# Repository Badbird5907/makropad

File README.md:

# Makropad

Makropad is my attempt at a custom macropad, inspired by the [Stream Deck Plus](https://www.elgato.com/ca/en/p/stream-deck-plus-black).
It uses Kaith Choc v2 switches, 2 encoders, powered by a RP2040.

A user-friendly BOM can be found [here](https://github.com/Badbird5907/makropad/blob/master/PCB/BOM.md)

## Features
- 2 rotary encoders
- 10 backlit keys
- 128x32 OLED display

## Screenshots

3D Renders of the Cherry MX switch version (made with Shapr3D):

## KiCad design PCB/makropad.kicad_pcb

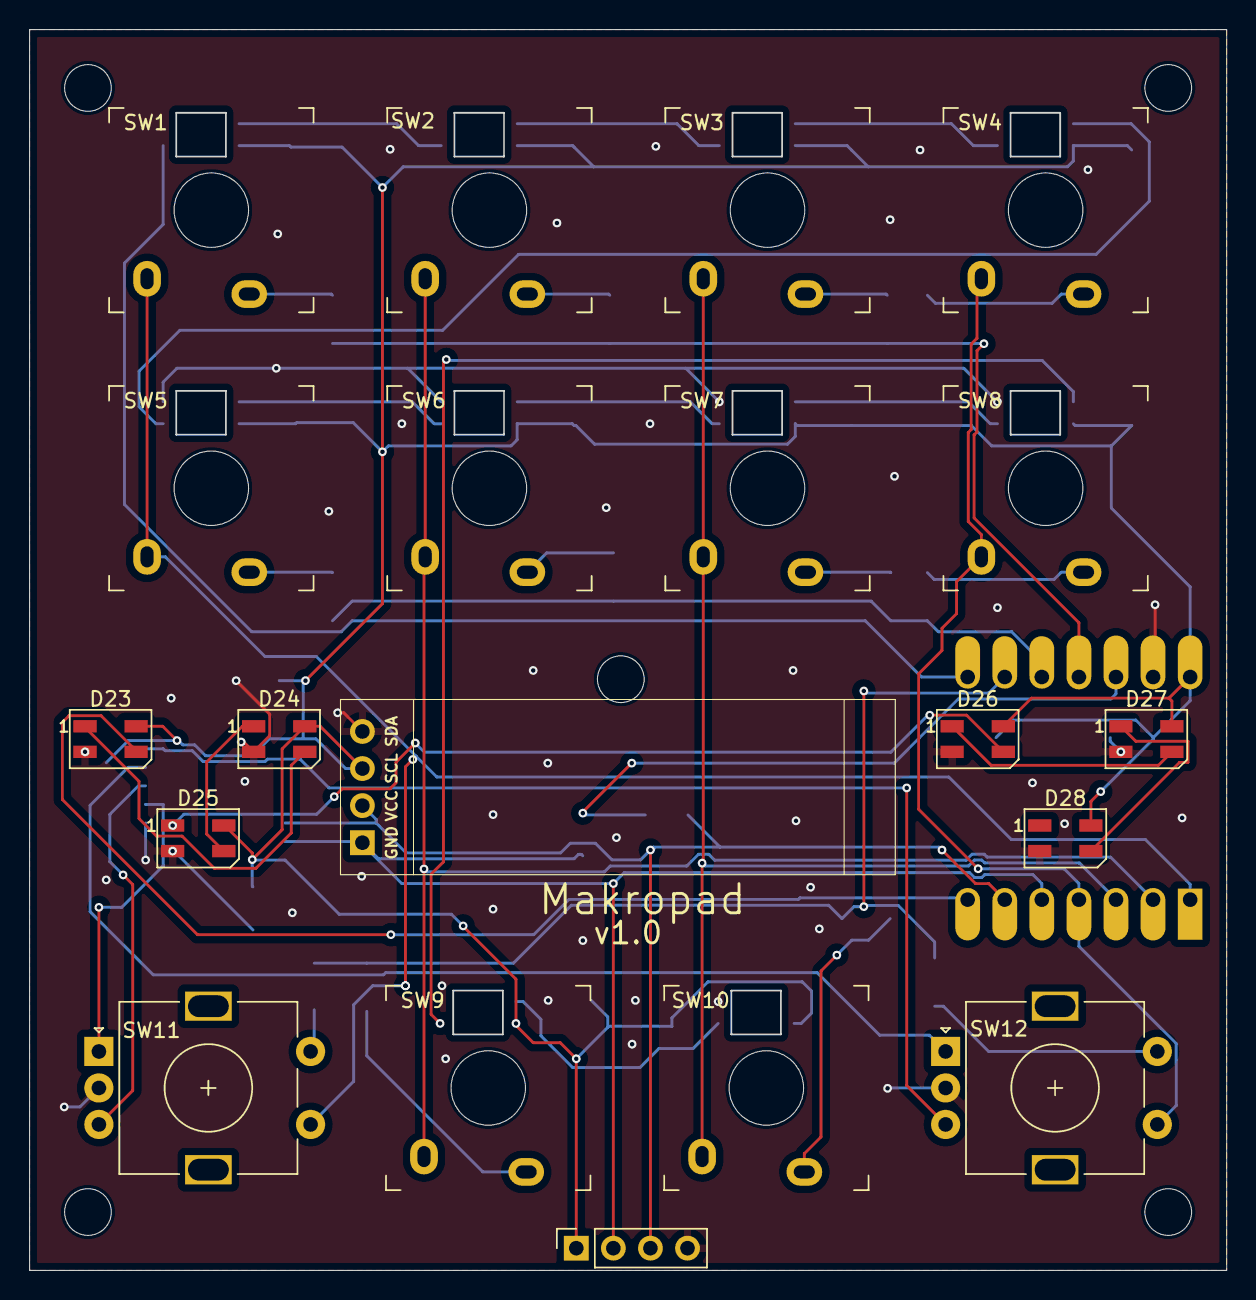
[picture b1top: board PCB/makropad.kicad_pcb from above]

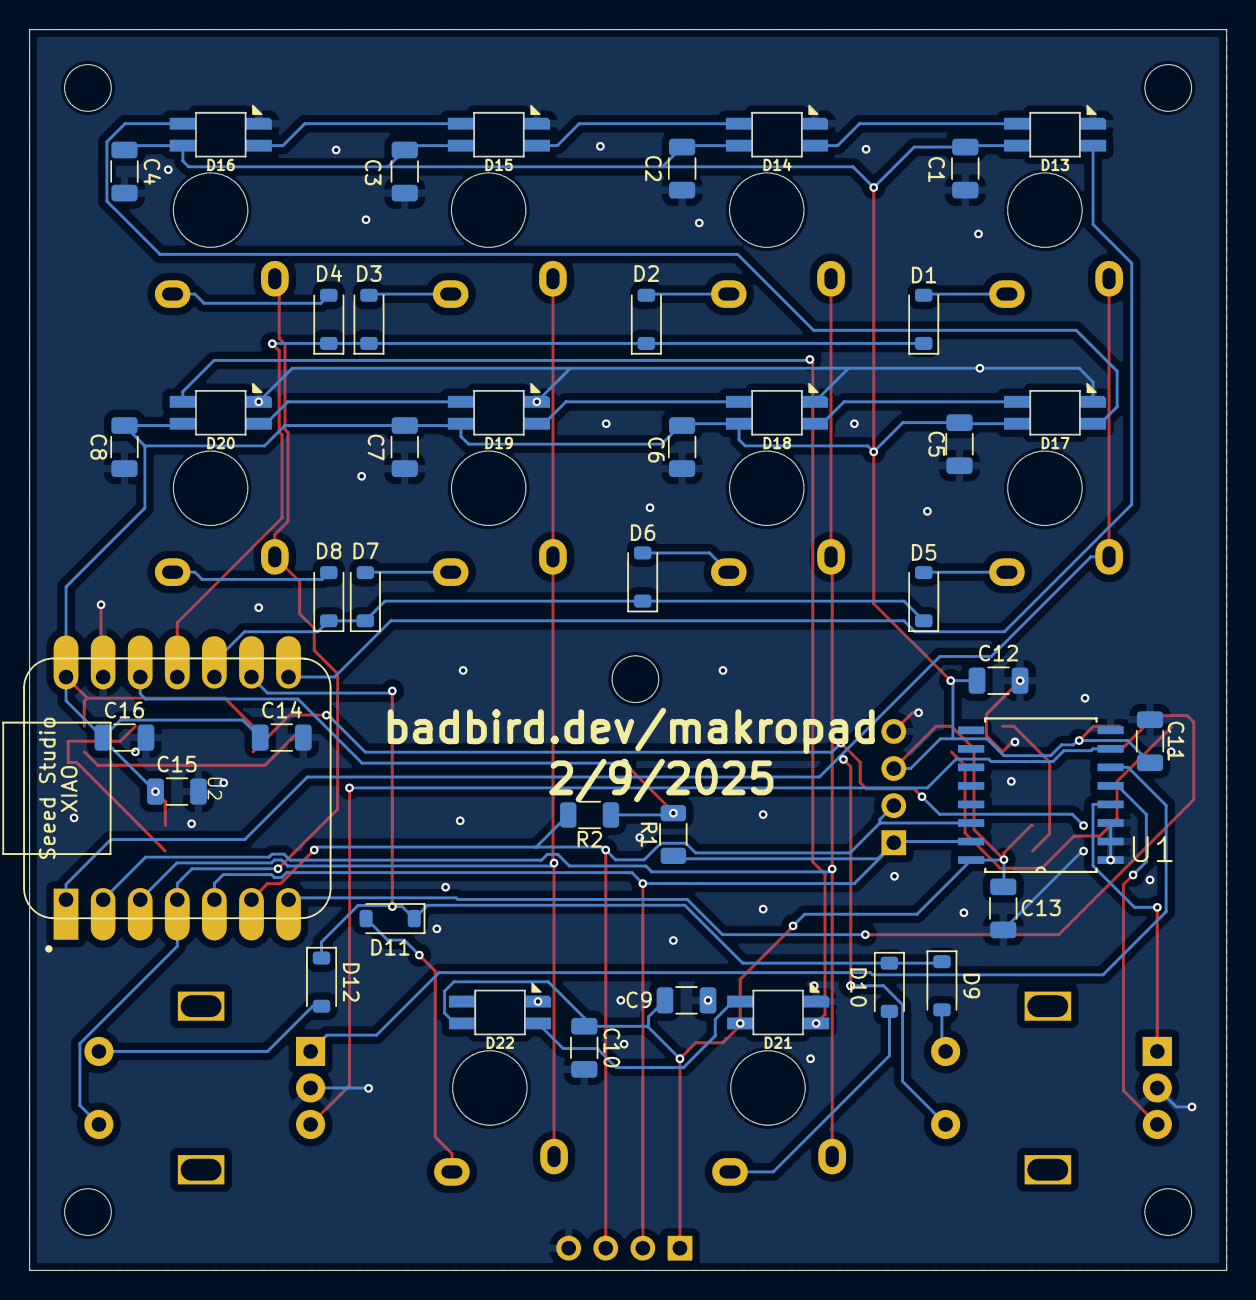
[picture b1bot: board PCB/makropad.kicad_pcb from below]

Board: 2 copper layers, 82.0 x 85.0 mm, 67 parts (43 on the bottom side), 44 nets.

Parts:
C1, C2, C3, C4, C5, C6, C7, C8, C9, C10, C11, C12, C13, C14, C15, C16: 0.1uF; C_1206_3216Metric
D1, D2, D3, D4, D5, D6, D7, D8, D9, D10, D11, D12: D; D_SOD-123
D13, D14, D15, D16, D17, D18, D19, D20, D21, D22: SK6812; SK6812MINI-E
D23, D24, D25, D26, D27, D28: SK6812; LED_SK6812MINI_PLCC4_3.5x3.5mm_P1.75mm
J1: OLED_DISPLAY; SSD1306-0.91-OLED-4pin-128x32
J2: Conn_01x04; 4pin
MH1, MH2, MH3, MH4, MH5: MountingHole_3.2mm_M3
R1, R2: 10k; R_1206_3216Metric
SW1, SW2, SW3, SW4, SW5, SW6, SW7, SW8, SW9, SW10: SW_Push_45deg; Gateron Low Profile Switch 2.0
SW11, SW12: RotaryEncoder_Switch; encoder
U1: PCF8574A; SOIC127P1032X265-16N
U2: MOUDLE-SEEEDUINO-XIAO; XIAO-Generic-Hybrid-14P-2.54-21X17.8MM

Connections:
+3.3V: R1.2, R2.2, U2.12 (3V3)
COL0: SW1.1, SW5.1, SW11.S1, U2.1 (PA02_A0_D0)
COL1: SW2.1, SW6.1, SW9.1, U2.2 (PA4_A1_D1)
COL2: SW3.1, SW7.1, SW10.1, U2.3 (PA10_A2_D2)
COL3: SW4.1, SW8.1, SW12.S1, U2.4 (PA11_A3_D3)
ENC_1_A: SW11.A, U1.4 (P0)
ENC_1_B: SW11.B, U1.5 (P1)
ENC_1_SWA: D9.2 (A), SW11.S2
ENC_2_A: SW12.A, U1.6 (P2)
ENC_2_B: SW12.B, U1.7 (P3)
ENC_2_SWA: D12.2 (A), SW12.S2
GND: C1.2, C2.2, C3.2, C4.2, C5.2, C6.2, C7.2, C8.2, C9.2, C10.2, C11.2, C12.2, C13.2, C14.2, C15.2, C16.2, D13.2 (VSS), D14.2 (VSS), D15.2 (VSS), D16.2 (VSS), D17.2 (VSS), D18.2 (VSS), D19.2 (VSS), D20.2 (VSS), D21.2 (VSS), D22.2 (VSS), D23.2 (VSS), D24.2 (VSS), D25.2 (VSS), D26.2 (VSS), D27.2 (VSS), D28.2 (VSS), J1.4, J2.4, SW11.C, SW12.C, U1.1 (A0), U1.2 (A1), U1.3 (A2), U1.8 (VSS), U2.13 (GND)
I2C_SCL: J1.2, J2.3, R2.1, U1.14 (SCL), U2.6 (PA9_A5_D5_SCL)
I2C_SDA: J1.1, J2.2, R1.1, U1.15 (SDA), U2.5 (PA8_A4_D4_SDA)
unnamed: D1.2 (A), SW1.2
unnamed: D2.2 (A), SW2.2
unnamed: D3.2 (A), SW3.2
unnamed: D4.2 (A), SW4.2
unnamed: D5.2 (A), SW5.2
unnamed: D6.2 (A), SW6.2
unnamed: D7.2 (A), SW7.2
unnamed: D8.2 (A), SW8.2
unnamed: D10.2 (A), SW9.2
unnamed: D11.2 (A), SW10.2
unnamed: D13.1 (DOUT), D14.3 (DIN)
unnamed: D14.1 (DOUT), D15.3 (DIN)
unnamed: D15.1 (DOUT), D16.3 (DIN)
unnamed: D16.1 (DOUT), D17.3 (DIN)
unnamed: D17.1 (DOUT), D18.3 (DIN)
unnamed: D18.1 (DOUT), D19.3 (DIN)
unnamed: D19.1 (DOUT), D20.3 (DIN)
unnamed: D20.1 (DOUT), D21.3 (DIN)
unnamed: D21.1 (DOUT), D22.3 (DIN)
unnamed: D23.1 (DOUT), D24.3 (DIN)
unnamed: D24.1 (DOUT), D25.3 (DIN)
unnamed: D25.1 (DOUT), D26.3 (DIN)
unnamed: D26.1 (DOUT), D27.3 (DIN)
unnamed: D27.1 (DOUT), D28.3 (DIN)
RGB: D13.3 (DIN), U2.8 (PB09_A7_D7_RX)
ROW0: D1.1 (K), D2.1 (K), D3.1 (K), D4.1 (K), U2.11 (PA6_A10_D10_MOSI)
ROW1: D5.1 (K), D6.1 (K), D7.1 (K), D8.1 (K), U2.10 (PA5_A9_D9_MISO)
ROW2: D9.1 (K), D10.1 (K), D11.1 (K), D12.1 (K), U2.9 (PA7_A8_D8_SCK)
STATUS_LED: D23.3 (DIN), U2.7 (PB08_A6_D6_TX)
VCC: C1.1, C2.1, C3.1, C4.1, C5.1, C6.1, C7.1, C8.1, C9.1, C10.1, C11.1, C12.1, C13.1, C14.1, C15.1, C16.1, D13.4 (VDD), D14.4 (VDD), D15.4 (VDD), D16.4 (VDD), D17.4 (VDD), D18.4 (VDD), D19.4 (VDD), D20.4 (VDD), D21.4 (VDD), D22.4 (VDD), D23.4 (VDD), D24.4 (VDD), D25.4 (VDD), D26.4 (VDD), D27.4 (VDD), D28.4 (VDD), J1.3, J2.1, U1.16 (VDD), U2.14 (5V)

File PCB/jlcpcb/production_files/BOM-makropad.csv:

Comment,Designator,Footprint,LCSC,Quantity
10k,"R1,R2,R3,R4,R5,R6",R_1206_3216Metric,C17902,6
D,"D1,D10,D11,D12,D2,D3,D4,D5,D6,D7,D8,D9",D_SOD-123,C81598,12
PCF8574A,U1,SOIC127P1032X265-16N,C86832,1
SW_Push_45deg,SW2,Gateron Low Profile Switch 2.0,,1
OLED_DISPLAY,J1,SSD1306-0.91-OLED-4pin-128x32,,1
SW_Push_45deg,SW4,Gateron Low Profile Switch 2.0,,1
SW_Push_45deg,SW9,Gateron Low Profile Switch 2.0,,1
SW_Push_45deg,SW8,Gateron Low Profile Switch 2.0,,1
SW_Push_45deg,SW1,Gateron Low Profile Switch 2.0,,1
SW_Push_45deg,SW6,Gateron Low Profile Switch 2.0,,1
SW_Push_45deg,SW3,Gateron Low Profile Switch 2.0,,1
SW_Push_45deg,SW5,Gateron Low Profile Switch 2.0,,1
SW_Push_45deg,SW10,Gateron Low Profile Switch 2.0,,1
RotaryEncoder_Switch,SW11,encoder,,1
SW_Push_45deg,SW7,Gateron Low Profile Switch 2.0,,1
RotaryEncoder_Switch,SW12,encoder,,1
Conn_01x04,J2,4pin,,1
SK6812,D28,LED_SK6812_PLCC4_5.0x5.0mm_P3.2mm,,1
SK6812,D27,LED_SK6812_PLCC4_5.0x5.0mm_P3.2mm,,1
SK6812,D26,LED_SK6812_PLCC4_5.0x5.0mm_P3.2mm,,1
SK6812,D25,LED_SK6812_PLCC4_5.0x5.0mm_P3.2mm,,1
SK6812,D24,LED_SK6812_PLCC4_5.0x5.0mm_P3.2mm,,1
SK6812,D23,LED_SK6812_PLCC4_5.0x5.0mm_P3.2mm,,1
SK6812,D22,SK6812MINI-E,,1
SK6812,D21,SK6812MINI-E,,1
SK6812,D20,SK6812MINI-E,,1
SK6812,D19,SK6812MINI-E,,1
SK6812,D18,SK6812MINI-E,,1
SK6812,D17,SK6812MINI-E,,1
SK6812,D16,SK6812MINI-E,,1
SK6812,D15,SK6812MINI-E,,1
SK6812,D14,SK6812MINI-E,,1
SK6812,D13,SK6812MINI-E,,1
MOUDLE-SEEEDUINO-XIAO,U2,XIAO-Generic-Hybrid-14P-2.54-21X17.8MM,,1

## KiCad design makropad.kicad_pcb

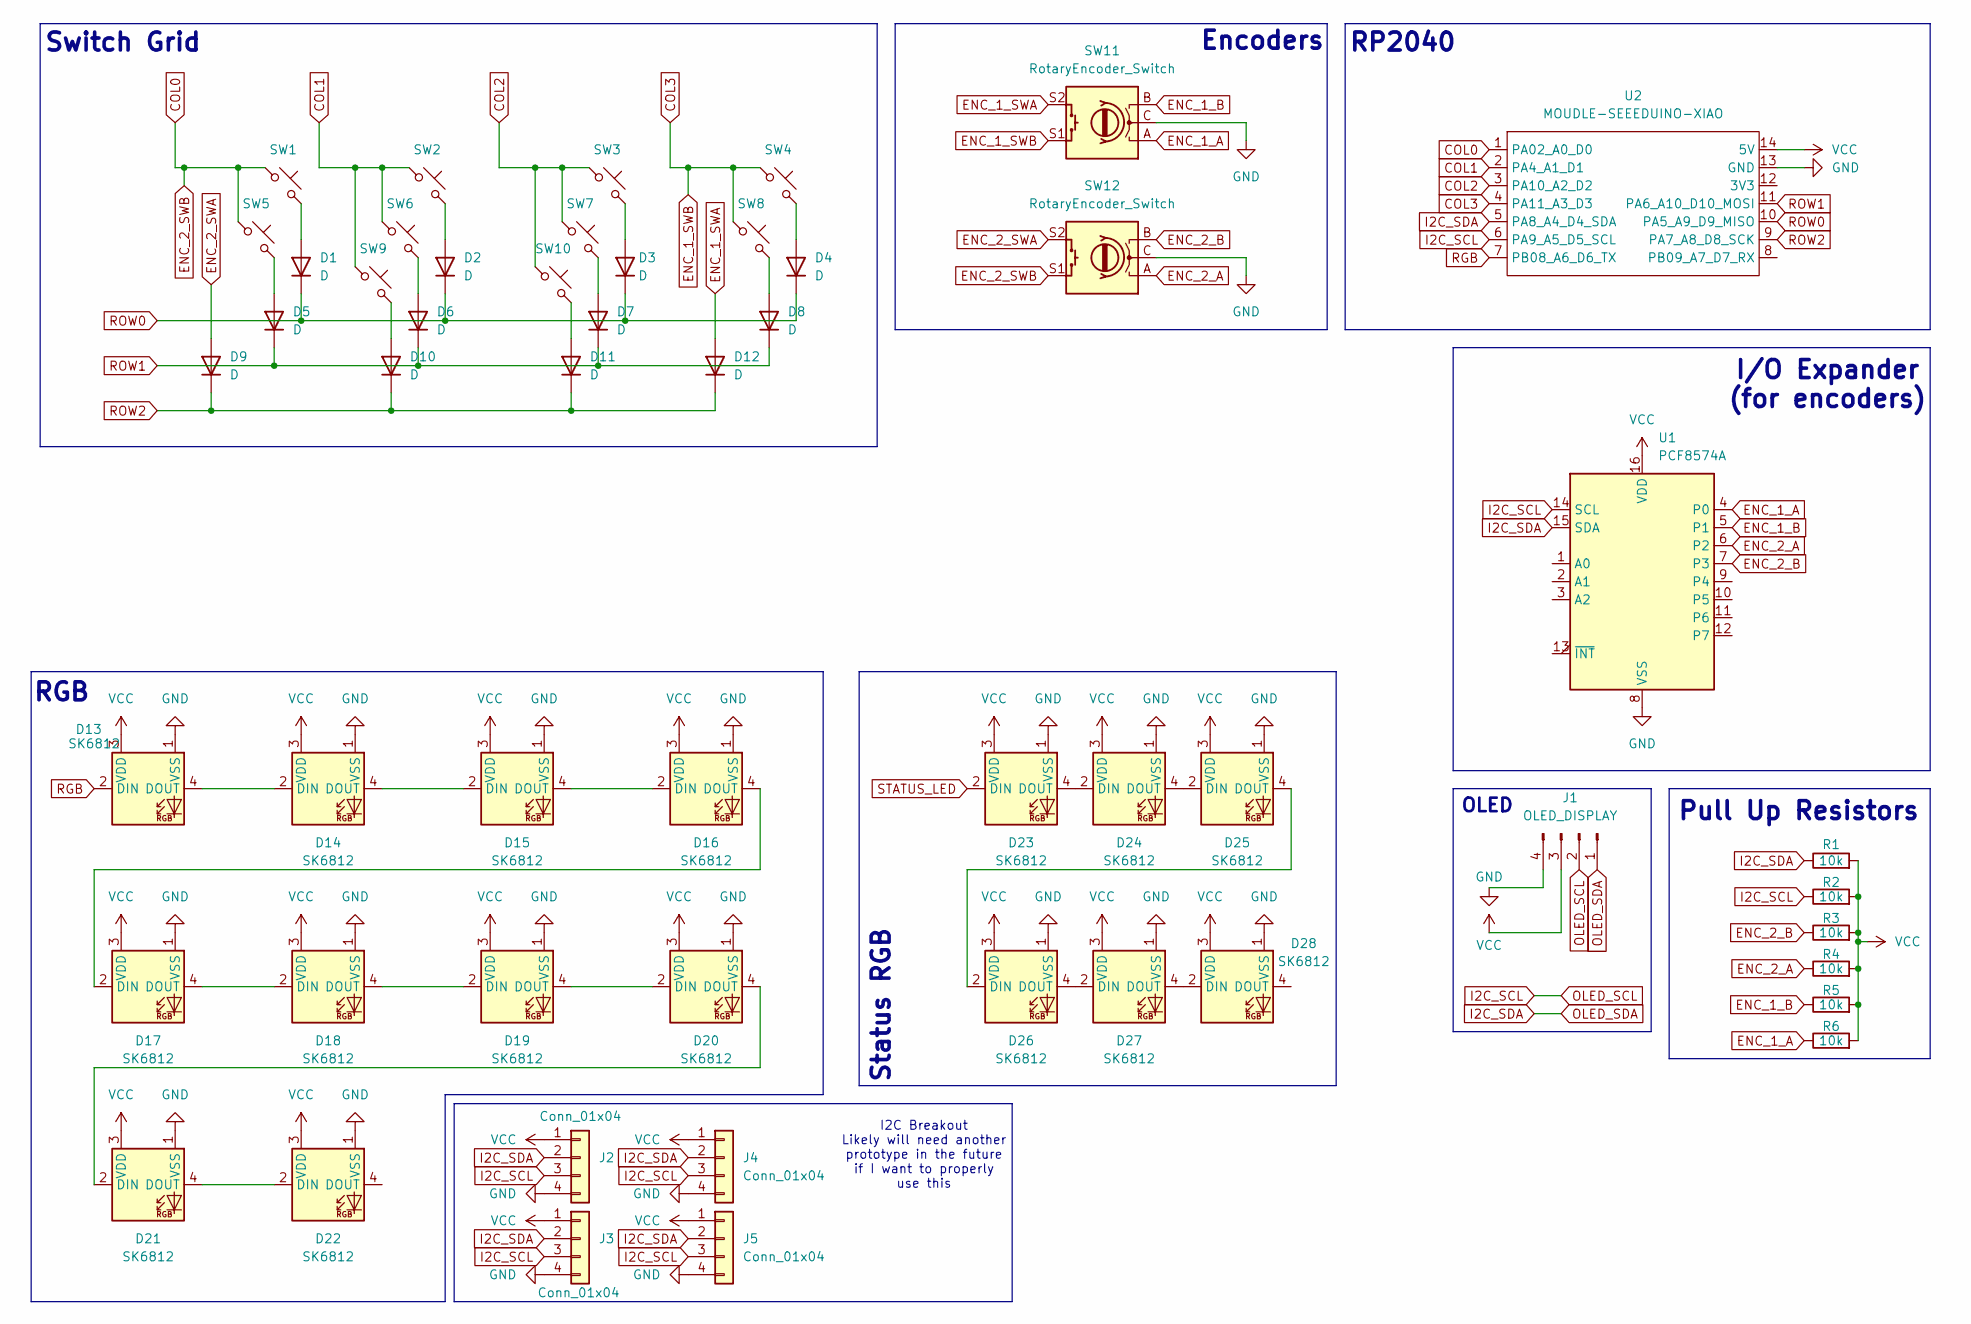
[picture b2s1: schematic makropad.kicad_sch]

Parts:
D1, D2, D3, D4, D5, D6, D7, D8, D9, D10, D11, D12: D; D_1206_3216Metric
D13, D14, D15, D16, D17, D18, D19, D20, D21, D22: SK6812; SK6812MINI-E
D23, D24, D25, D26, D27, D28: SK6812; LED_SK6812_PLCC4_5.0x5.0mm_P3.2mm
J1: OLED_DISPLAY; SSD1306-0.91-OLED-4pin-128x32
J2, J3, J4, J5: Conn_01x04; 4pin
R1, R2, R3, R4, R5, R6: 10k; R_1206_3216Metric
SW1, SW2, SW3, SW4, SW5, SW6, SW7, SW8, SW9, SW10: SW_Push_45deg; MX-Solderable-1U
SW11, SW12: RotaryEncoder_Switch; encoder
U1: PCF8574A; SOIC127P1032X265-16N
U2: MOUDLE-SEEEDUINO-XIAO; XIAO-Generic-Hybrid-14P-2.54-21X17.8MM

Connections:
COL0: SW1.1, SW5.1, SW12.S1, U2.1 (PA02_A0_D0)
COL1: SW2.1, SW6.1, SW9.1, U2.2 (PA4_A1_D1)
COL2: SW3.1, SW7.1, SW10.1, U2.3 (PA10_A2_D2)
COL3: SW4.1, SW8.1, SW11.S1, U2.4 (PA11_A3_D3)
ENC_1_A: R6.1, SW11.A, U1.4 (P0)
ENC_1_B: R5.1, SW11.B, U1.5 (P1)
ENC_1_SWA: D12.2 (A), SW11.S2
ENC_2_A: R4.1, SW12.A, U1.6 (P2)
ENC_2_B: R3.1, SW12.B, U1.7 (P3)
ENC_2_SWA: D9.2 (A), SW12.S2
GND: D13.1 (VSS), D14.1 (VSS), D15.1 (VSS), D16.1 (VSS), D17.1 (VSS), D18.1 (VSS), D19.1 (VSS), D20.1 (VSS), D21.1 (VSS), D22.1 (VSS), D23.1 (VSS), D24.1 (VSS), D25.1 (VSS), D26.1 (VSS), D27.1 (VSS), D28.1 (VSS), J1.4, J2.4, J3.4, J4.4, J5.4, SW11.C, SW12.C, U1.8 (VSS), U2.13 (GND)
I2C_SCL: J1.2, J2.3, J3.3, J4.3, J5.3, R2.1, U1.14 (SCL), U2.6 (PA9_A5_D5_SCL)
I2C_SDA: J1.1, J2.2, J3.2, J4.2, J5.2, R1.1, U1.15 (SDA), U2.5 (PA8_A4_D4_SDA)
unnamed: D1.2 (A), SW1.2
unnamed: D2.2 (A), SW2.2
unnamed: D3.2 (A), SW3.2
unnamed: D4.2 (A), SW4.2
unnamed: D5.2 (A), SW5.2
unnamed: D6.2 (A), SW6.2
unnamed: D7.2 (A), SW7.2
unnamed: D8.2 (A), SW8.2
unnamed: D10.2 (A), SW9.2
unnamed: D11.2 (A), SW10.2
unnamed: D13.4 (DOUT), D14.2 (DIN)
unnamed: D14.4 (DOUT), D15.2 (DIN)
unnamed: D15.4 (DOUT), D16.2 (DIN)
unnamed: D16.4 (DOUT), D17.2 (DIN)
unnamed: D17.4 (DOUT), D18.2 (DIN)
unnamed: D18.4 (DOUT), D19.2 (DIN)
unnamed: D19.4 (DOUT), D20.2 (DIN)
unnamed: D20.4 (DOUT), D21.2 (DIN)
unnamed: D21.4 (DOUT), D22.2 (DIN)
unnamed: D23.4 (DOUT), D24.2 (DIN)
unnamed: D24.4 (DOUT), D25.2 (DIN)
unnamed: D25.4 (DOUT), D26.2 (DIN)
unnamed: D26.4 (DOUT), D27.2 (DIN)
unnamed: D27.4 (DOUT), D28.2 (DIN)
RGB: D13.2 (DIN), U2.7 (PB08_A6_D6_TX)
ROW0: D1.1 (K), D2.1 (K), D3.1 (K), D4.1 (K), U2.10 (PA5_A9_D9_MISO)
ROW1: D5.1 (K), D6.1 (K), D7.1 (K), D8.1 (K), U2.11 (PA6_A10_D10_MOSI)
ROW2: D9.1 (K), D10.1 (K), D11.1 (K), D12.1 (K), U2.9 (PA7_A8_D8_SCK)
STATUS_LED: D23.2 (DIN)
VCC: D13.3 (VDD), D14.3 (VDD), D15.3 (VDD), D16.3 (VDD), D17.3 (VDD), D18.3 (VDD), D19.3 (VDD), D20.3 (VDD), D21.3 (VDD), D22.3 (VDD), D23.3 (VDD), D24.3 (VDD), D25.3 (VDD), D26.3 (VDD), D27.3 (VDD), D28.3 (VDD), J1.3, J2.1, J3.1, J4.1, J5.1, R1.2, R2.2, R3.2, R4.2, R5.2, R6.2, U1.16 (VDD), U2.14 (5V)

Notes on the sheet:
RGB
Switch Grid
RP2040
OLED
I2C Breakout Likely will need another prototype in the future if I want to properly use this
Encoders
Status RGB
I/O Expander (for encoders)
Pull Up Resistors

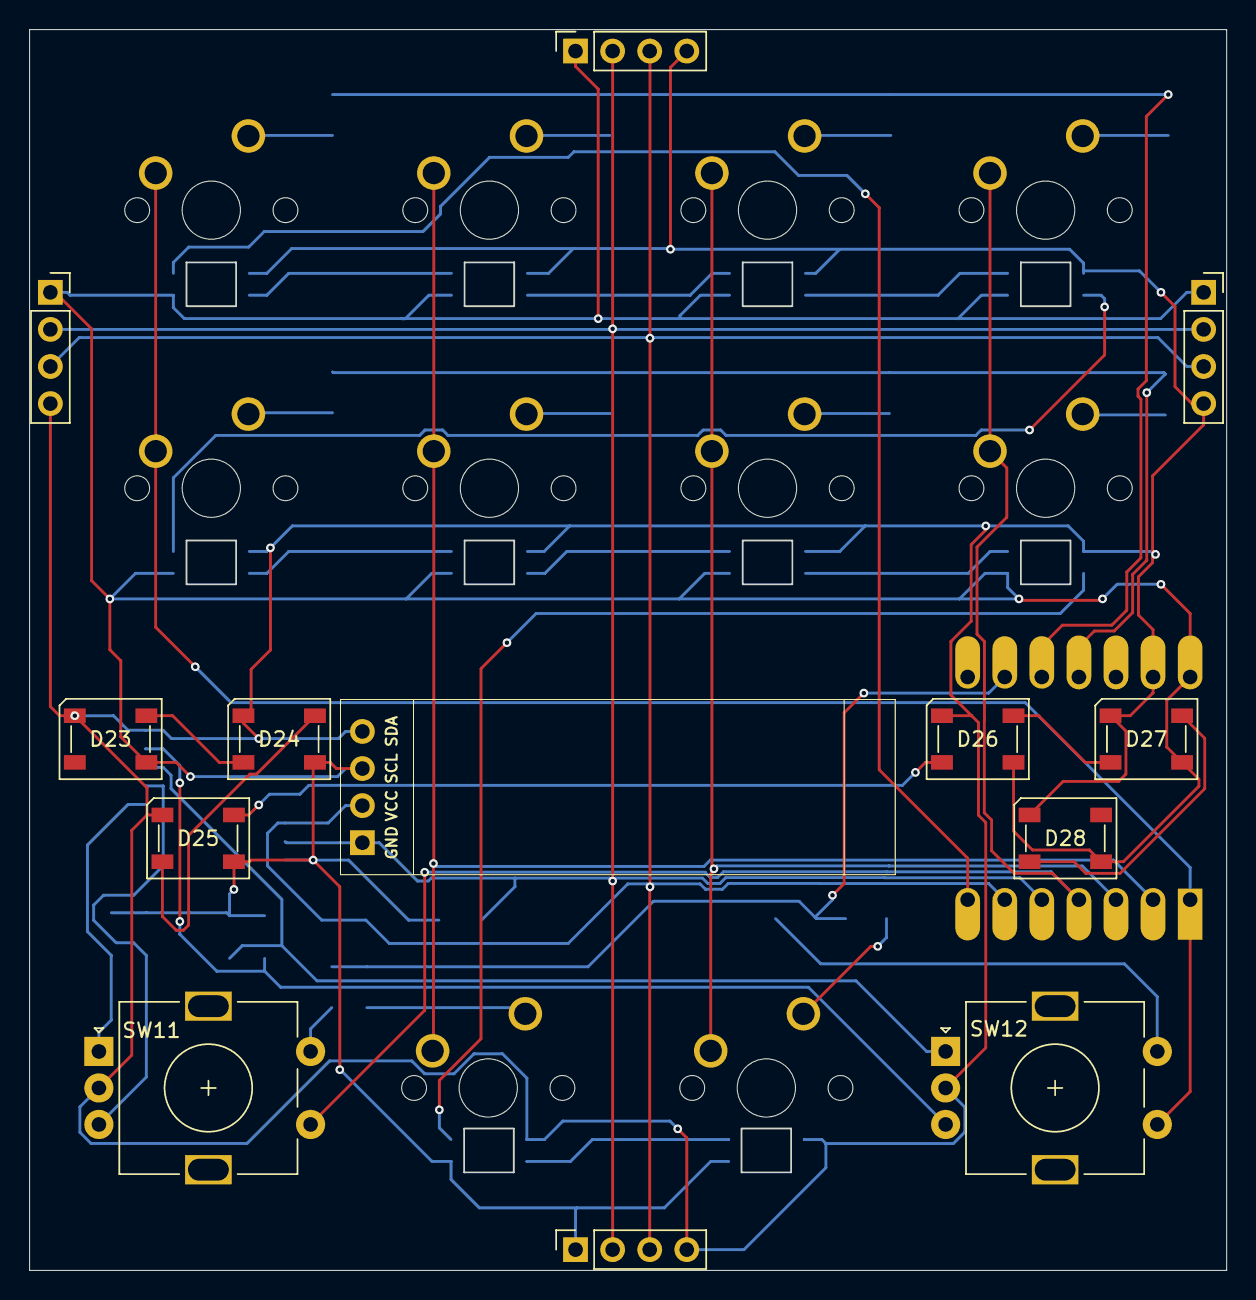
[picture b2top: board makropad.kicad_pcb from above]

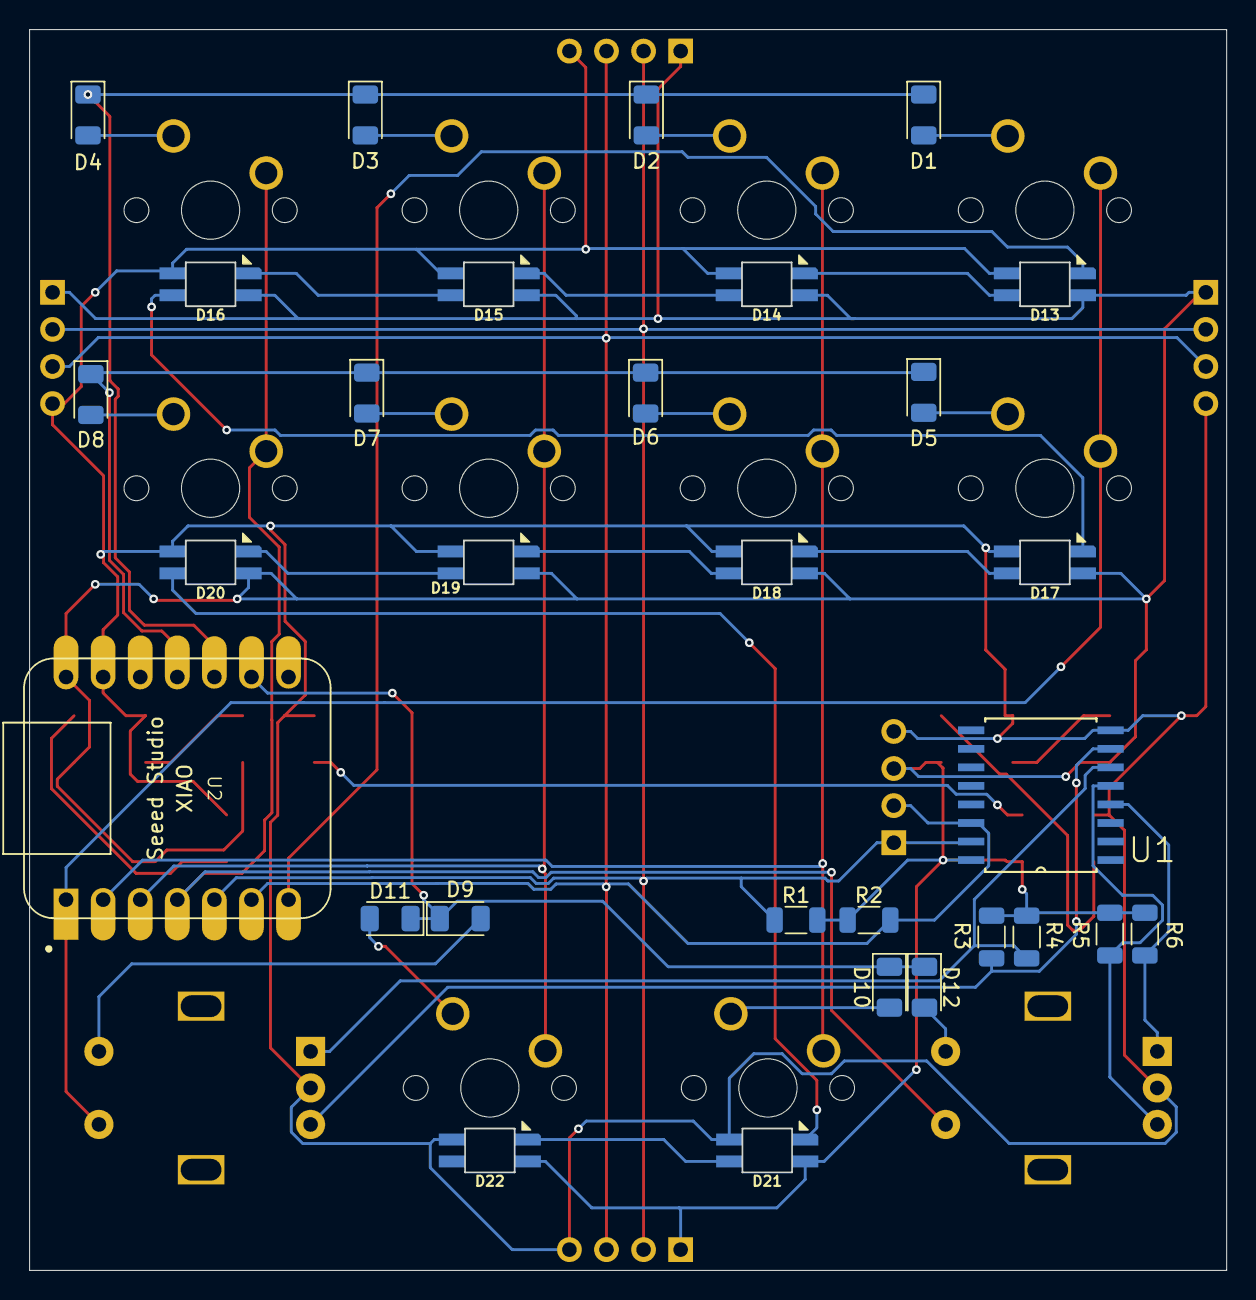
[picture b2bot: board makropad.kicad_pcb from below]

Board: 2 copper layers, 82.0 x 85.0 mm, 53 parts (30 on the bottom side), 42 nets.

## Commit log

2025-01-31 Finish pcb
2025-02-09 feat: finish pcb placement
2025-02-09 feat: fully route pcb
2025-02-09 feat: add 3d renders
2025-02-09 chore: remove backups
2025-02-09 feat: add backups folder to gitignore
2025-02-09 chore: move kicad files to pcb folder
2025-02-09 feat: select jlc parts
2025-02-09 feat: switch to SOD-123 diodes
2025-02-09 fix: fix DRC
2025-02-09 feat: generate production gerbers
2025-02-09 feat: finish sikscreen & and pcb prod files
2025-02-09 feat: finalize pcb design and 3d renders
2025-02-09 fix: led spacing on bottom switches
2025-02-10 feat: add bom
2025-02-10 feat: add mounting holes and move around some components & silkscreen
2025-02-11 feat: switch to gateron low profile
2025-02-11 feat: add mounting holes for new design
2025-02-12 stuff
2025-02-12 remove lock files
2025-02-13 feat: pull up i2c lines to 3.3v and remove encoder pull ups
2025-02-13 fuck
2025-02-14 finally finish up pcb and fix led wiring
2025-02-14 generate production files
2025-02-14 fix: clarify gateron switches in bom
2025-02-14 fix some stuff + firmware
2025-02-14 Generate all production files
2025-02-15 feat: switch to choc v2 switches
2025-02-15 chore: update readme
2025-02-15 Update images
2025-02-15 Update production files
